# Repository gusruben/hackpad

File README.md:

# I made a macro pad.

Here it is:

## BOM

- 9x Cherry MX Switches
- 9x DSA Keycaps
- 9x 1N4148 DO-35 Diodes
- 1x EC11 Rotary Encoder
- 1x XIAO RP2040
- 1x Case (printed)
- 1x Plate (printed)

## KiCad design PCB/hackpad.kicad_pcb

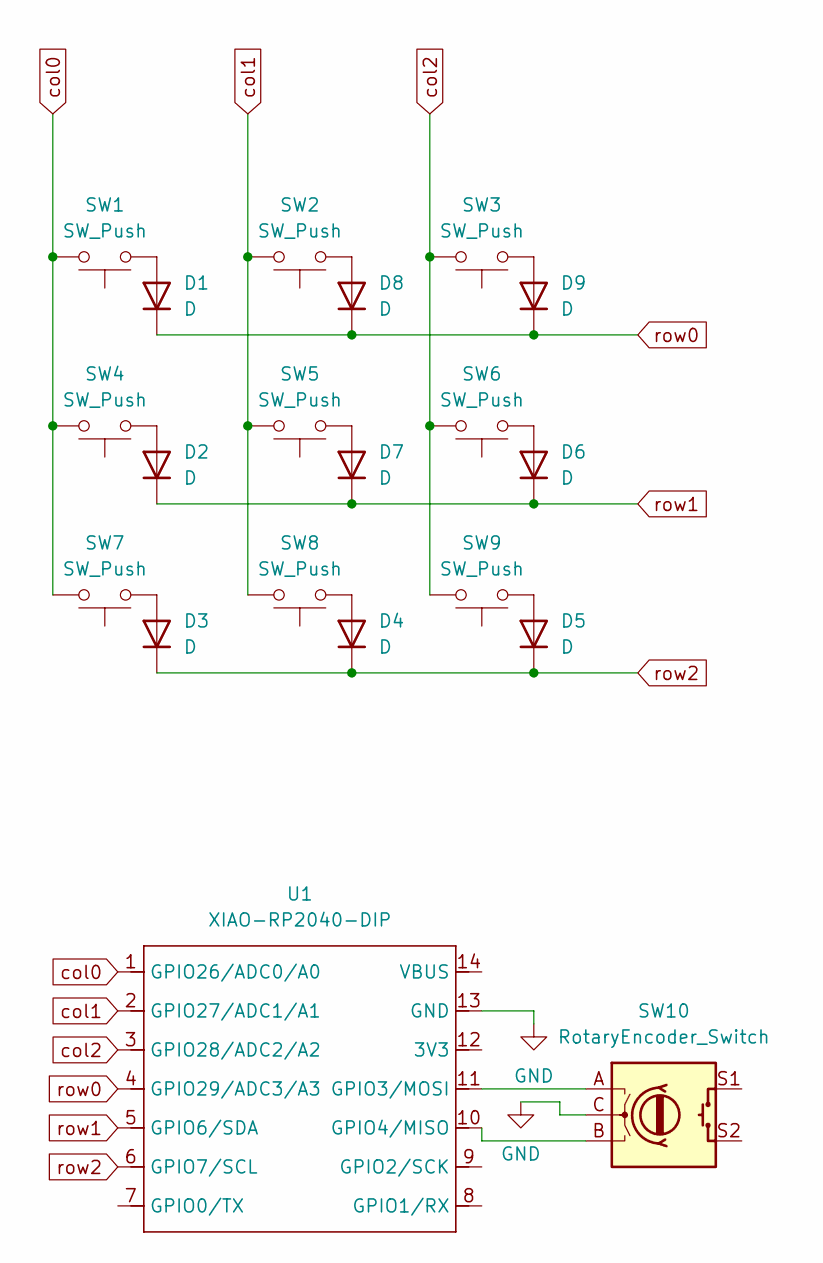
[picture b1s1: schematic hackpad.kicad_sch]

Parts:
D1, D2, D3, D4, D5, D6, D7, D8, D9: D; D_T-1_P5.08mm_Horizontal
SW1, SW2, SW3, SW4, SW5, SW6, SW7, SW8, SW9: SW_Push; SW_Cherry_MX_1.00u_PCB
SW10: RotaryEncoder_Switch; RotaryEncoder_Alps_EC11E-Switch_Vertical_H20mm_CircularMoun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
U1: XIAO-RP2040-DIP

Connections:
GND: SW10.C, U1.13 (GND)
unnamed: D1.2 (A), SW1.1
unnamed: D2.2 (A), SW4.1
unnamed: D3.2 (A), SW7.1
unnamed: D4.2 (A), SW8.1
unnamed: D5.2 (A), SW9.1
unnamed: D6.2 (A), SW6.1
unnamed: D7.2 (A), SW5.1
unnamed: D8.2 (A), SW2.1
unnamed: D9.2 (A), SW3.1
unnamed: SW10.A, U1.11 (GPIO3/MOSI)
unnamed: SW10.B, U1.10 (GPIO4/MISO)
col0: SW1.2, SW4.2, SW7.2, U1.1 (GPIO26/ADC0/A0)
col1: SW2.2, SW5.2, SW8.2, U1.2 (GPIO27/ADC1/A1)
col2: SW3.2, SW6.2, SW9.2, U1.3 (GPIO28/ADC2/A2)
row0: D1.1 (K), D8.1 (K), D9.1 (K), U1.4 (GPIO29/ADC3/A3)
row1: D2.1 (K), D6.1 (K), D7.1 (K), U1.5 (GPIO6/SDA)
row2: D3.1 (K), D4.1 (K), D5.1 (K), U1.6 (GPIO7/SCL)

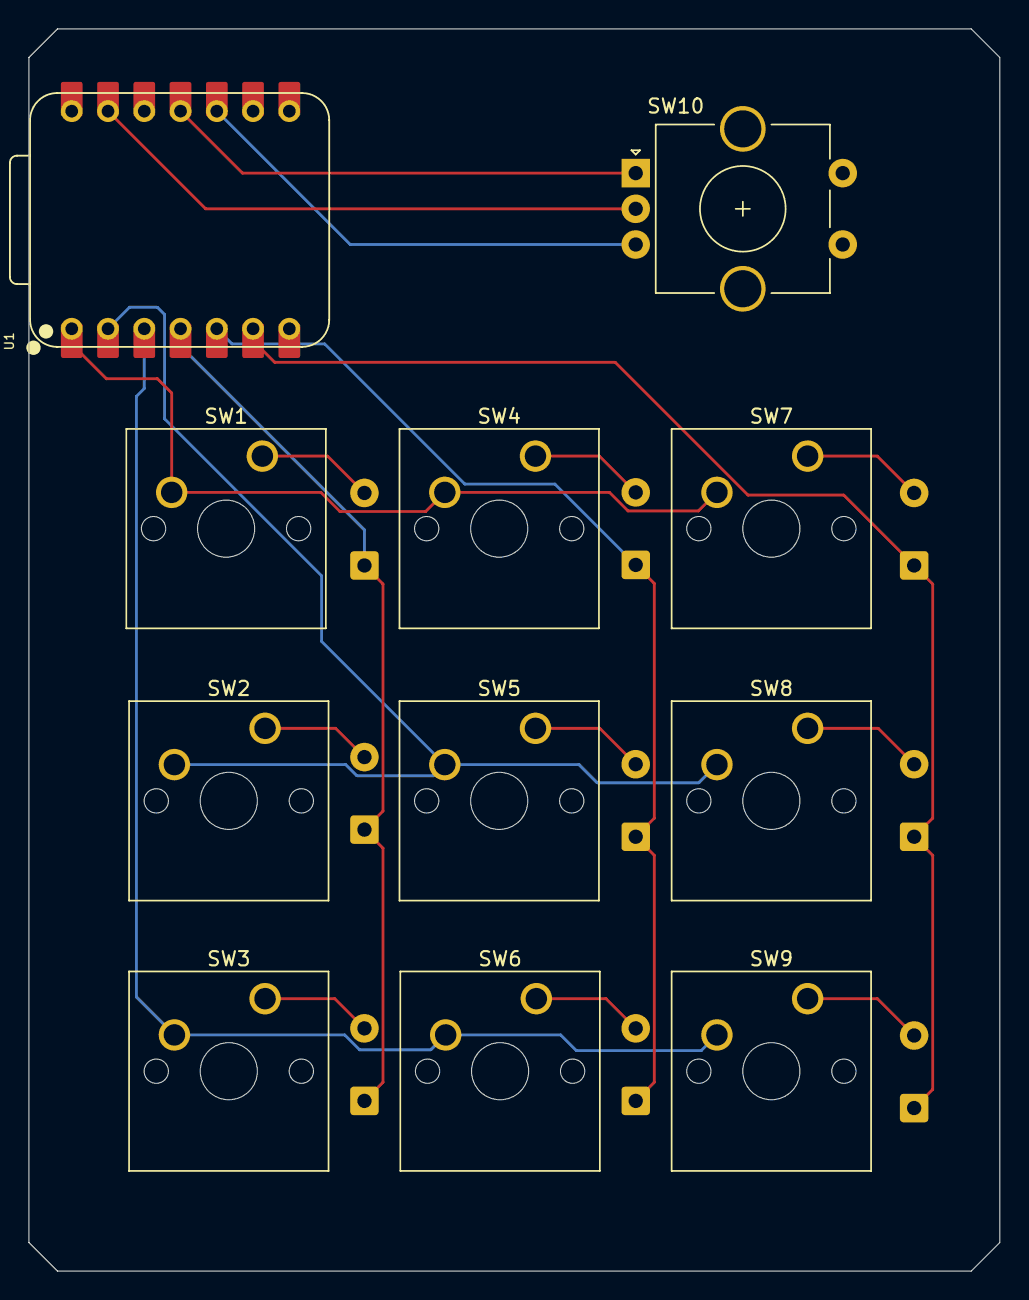
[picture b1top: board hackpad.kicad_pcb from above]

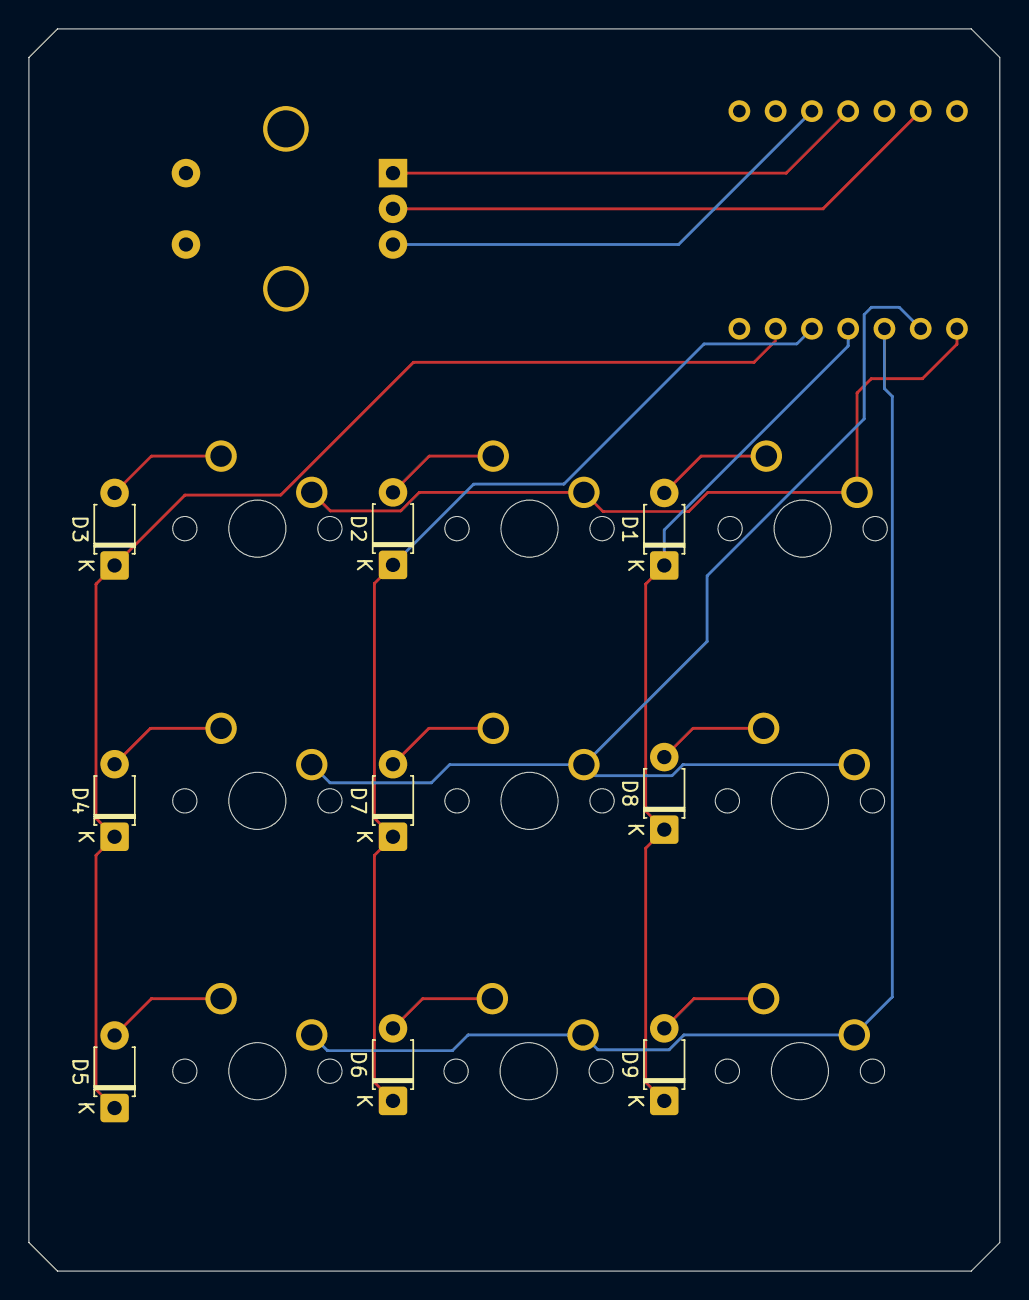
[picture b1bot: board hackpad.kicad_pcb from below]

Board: 2 copper layers, 68.0 x 87.0 mm, 20 parts (9 on the bottom side), 18 nets.

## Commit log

2025-07-07 Rename PCB folder
